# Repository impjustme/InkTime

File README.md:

# InkTime

InkTime este un smartwatch open-source cu consum redus, construit in jurul microcontroller-ului nRF52840, cu ecran e-paper, alimentare din baterie Li-Po, incarcare prin USB-C, monitorizare baterie, IMU si feedback haptic. Platforma a fost proiectata pentru autonomie buna, dimensiuni compacte si integrare mecanica intr-o carcasa dedicata.

## Diagrama bloc

```
                                +----------------------+
                                |       USB-C          |
                                |   alimentare / USB   |
                                +----------+-----------+
                                           |
                                           v
                                +----------------------+
                                |   ESD Protection     |
                                |    USBLC6-2SC6Y      |
                                +----------+-----------+
                                           |
                                           v
                                +----------------------+
                                |  Li-Po Charger       |
                                |    BQ25180YBGR       |
                                +----+------------+----+
                                     |            |
                                     |            +--------------------+
                                     |                                 |
                                     v                                 v
                           +-------------------+             +-------------------+
                           |    Li-Po Battery  |             |   Fuel Gauge      |
                           |     LP502030      |<-- I2C ---> |    MAX17048       |
                           +---------+---------+             +-------------------+
                                     |
                                     v
                           +-------------------+
                           |  Buck-Boost DC/DC |
                           |    RT6160AWSC     |
                           +---------+---------+
                                     |
                                   3V3/VREG
                                     |
        +----------------------------+------------------------------+
        |                            |                              |
        v                            v                              v
+---------------+          +-------------------+          +-------------------+
|   nRF52840    |<--I2C--->|      BMA423       |<--I2C--->|     DRV2605       |
| BLE MCU       |          |       IMU         |          |   Haptic Driver   |
+-------+-------+          +-------------------+          +---------+---------+
        |                                                              |
        | SPI + GPIO                                                    v
        v                                                      +----------------+
+-------------------+                                          | Vibration Motor |
| 1.54" E-Paper     |                                          |    10 x 2.7 mm  |
| via FPC connector |                                          +----------------+
+-------------------+
        |
        +--> boost / gate drive pentru EPD:
             MOSFET-uri + diode Schottky + inductoare + condensatori
```

## BoM

| Componenta       | Part number / Valoare  | Rol                           | Link JLC / sursa              | Datasheet                                                                                                                                                                              |
| ---------------- | ---------------------- | ----------------------------- | ----------------------------- | -------------------------------------------------------------------------------------------------------------------------------------------------------------------------------------- |
| MCU              | nRF52840               | microcontroller principal BLE | JLC Parts / external sourcing | [https://infocenter.nordicsemi.com/pdf/nRF52840_PS_v1.1.pdf](https://infocenter.nordicsemi.com/pdf/nRF52840_PS_v1.1.pdf)                                                               |
| PMIC charger     | BQ25180YBGR            | incarcare Li-Po prin USB-C    | JLC Parts                     | [https://www.ti.com/lit/ds/symlink/bq25180.pdf](https://www.ti.com/lit/ds/symlink/bq25180.pdf)                                                                                         |
| DC/DC            | RT6160AWSC             | conversie VBAT -> 3V3/VREG    | JLC Parts / external sourcing | [https://www.richtek.com/assets/product_file/RT6160A/DS6160A-05.pdf](https://www.richtek.com/assets/product_file/RT6160A/DS6160A-05.pdf)                                               |
| Fuel gauge       | MAX17048G+T10          | monitorizare baterie          | JLC Parts / external sourcing | [https://www.analog.com/media/en/technical-documentation/data-sheets/max17048-max17049.pdf](https://www.analog.com/media/en/technical-documentation/data-sheets/max17048-max17049.pdf) |
| IMU              | BMA423                 | accelerometru triaxial        | JLC Parts / external sourcing | [https://www.bosch-sensortec.com/products/motion-sensors/accelerometers/bma423/](https://www.bosch-sensortec.com/products/motion-sensors/accelerometers/bma423/)                       |
| Haptic driver    | DRV2605YZFR            | comanda motorului de vibratie | JLC Parts / external sourcing | [https://www.ti.com/lit/ds/symlink/drv2605.pdf](https://www.ti.com/lit/ds/symlink/drv2605.pdf)                                                                                         |
| ESD USB          | USBLC6-2SC6Y           | protectie ESD pentru USB      | JLC Parts                     | [https://www.st.com/resource/en/datasheet/usblc6-2.pdf](https://www.st.com/resource/en/datasheet/usblc6-2.pdf)                                                                         |
| Antena           | 2450AT18B100E          | antena 2.4 GHz                | external sourcing             | [https://www.johansontechnology.com/datasheets/antennas/2450AT18B100.pdf](https://www.johansontechnology.com/datasheets/antennas/2450AT18B100.pdf)                                     |
| Conector debug   | TC2030-IDC             | SWD / debugging               | external sourcing             | [https://www.tag-connect.com/product/tc2030-idc](https://www.tag-connect.com/product/tc2030-idc)                                                                                       |
| Conector display | 503480-2400            | conector FPC pentru e-paper   | external sourcing             | [https://www.molex.com/en-us/products/part-detail/5034802400](https://www.molex.com/en-us/products/part-detail/5034802400)                                                             |
| USB-C            | KH-TYPE-C-16P          | alimentare si interfata USB   | JLC Parts / external sourcing |                                                                                                                                                              |
| Cristal HF       | 32 MHz, SMD 2016       | ceas principal MCU            | JLC Parts / external sourcing |                                                                                                                                                                 |
| Cristal LF       | 32.768 kHz, SMD 3215   | RTC / low-power clock         | JLC Parts / external sourcing |                                                                                                                                                                 |
| MOSFET EPD       | SI1308EDL-T1-GE3       | comanda in etajul e-paper     | JLC Parts / external sourcing | [https://www.vishay.com/docs/68986/si1308edl.pdf](https://www.vishay.com/docs/68986/si1308edl.pdf)                                                                                     |
| MOSFET EPD       | DMG2305UX-7 / echiv.   | comanda in etajul e-paper     | JLC Parts / external sourcing | [https://www.diodes.com/assets/Datasheets/DMG2305UX.pdf](https://www.diodes.com/assets/Datasheets/DMG2305UX.pdf)                                                                       |
| Diode Schottky   | MBR0530                | etaj boost / redresare EPD    | JLC Parts / external sourcing | [https://www.onsemi.com/pdf/datasheet/mbr0530t1-d.pdf](https://www.onsemi.com/pdf/datasheet/mbr0530t1-d.pdf)                                                                           |
| Inductor power   | FTC252012SR47MBCA      | inductor pentru RT6160        | JLC Parts                     | [https://jlcpcb.com/partdetail/6763488-FTC252012SR47MBCA/C5832368](https://jlcpcb.com/partdetail/6763488-FTC252012SR47MBCA/C5832368)                                                   |
| Inductor EPD     | 68uH                   | inductor pentru boost EPD     | JLC Parts / external sourcing |                                                                                                                                                                  |
| Butoane          | EVP-AKE31A             | interfata utilizator          | JLC Parts / external sourcing |                                                                                                                                                                  |
| Baterie          | LP502030, 3.7V, 250mAh | sursa principala de energie   | external sourcing             |                                                                                                                                                       |
| Display          | 1.54" e-paper, 200x200 | afisaj principal              | external sourcing             |                                                                                                                                                                |
| Shaker           | 10 x 2.7 mm            | vibratie / feedback haptic    | external sourcing             |                                                                                                                                                               |
## Descriere hardware
1. Microcontroller principal

Sistemul este construit in jurul nRF52840, un microcontroller ARM Cortex-M4F cu BLE 5.x, suficient de performant pentru gestionarea afisajului e-paper, a senzorilor, a starii de baterie si a interfetei de utilizator.Pe partea de clock sunt folosite doua surse:

-un cristal de 32 MHz pentru clock-ul principal.

-un cristal de 32.768 kHz pentru RTC si scenarii low-power.

2. Alimentare si management energetic

Arhitectura de alimentare este impartita in trei blocuri.

BQ25180YBGR

Gestioneaza incarcarea bateriei Li-Po din USB-C. Intrarea de 5 V vine din VBUS, iar iesirea este conectata la bateria de o celula. Acest circuit este configurabil si monitorizabil, iar pinul de interrupt este dus catre MCU.

MAX17048

Monitorizeaza tensiunea si starea bateriei. Acesta comunica pe I2C cu microcontrollerul si expune un semnal de alerta pentru praguri critice sau schimbari de stare.

RT6160AWSC

Converteaza tensiunea bateriei intr-o alimentare stabila pentru sistemul digital. Acesta este blocul care alimenteaza rail-urile de lucru ale placii si perifericele sale.

In proiect, bateria nu este conectata printr-un conector JST clasic, ci direct la doua test pad-uri dedicate de pe PCB, una pentru VBAT si una pentru GND, pentru economie de spatiu.

3. Afisaj

Afisajul utilizat este un e-paper de 1.54", conectat printr-un conector FPC. Comunicatia cu MCU se face in principal prin SPI, iar pentru control sunt folosite si semnale GPIO dedicate:

CS

DC

RST

BUSY

Deoarece e-paper-ul necesita tensiuni si secvente specifice, exista un etaj discret dedicat pentru generarea si comutarea semnalelor de alimentare ale panelului, construit cu:

MOSFET-uri

diode Schottky

inductoare

condensatori de filtrare si bootstrap

4. IMU

BMA423 este accelerometrul triaxial folosit pentru detectie de miscare, pasi, gesturi si evenimente de trezire. Comunicatia se face pe I2C, iar semnalele de intrerupere sunt aduse pe GPIO-uri separate ale MCU-ului pentru reactii rapide si trezire din moduri low-power.

5. Feedback haptic

DRV2605 comanda un motor de vibratie compact. Comunicatia cu MCU se face pe I2C, iar activarea poate fi controlata si printr-un semnal GPIO dedicat. Acest bloc ofera feedback tactil pentru navigare, notificari si interactiuni de baza.

6. USB-C si protectie

Interfata USB-C este folosita pentru alimentare si, optional, interfata USB a microcontrollerului. Liniile sensibile sunt protejate cu USBLC6-2SC6Y. Liniile CC sunt terminate corespunzator pentru a permite functionarea corecta ca device.

7. RF si antena

Conectivitatea radio este realizata prin antena chip 2.4 GHz si o retea de matching RF. Antena este pozitionata la marginea PCB-ului, iar sub ea exista zona de keepout fara trasee si fara plan de masa, pentru a nu degrada performanta RF.

## Pini folositi

| Pin nRF52840  | Semnal         | Destinatie                                     | Motiv                             |
| ------------- | -------------- | ---------------------------------------------- | --------------------------------- |
| P0.00 / XL1   | XL1            | cristal 32.768 kHz                             | clock low-power / RTC             |
| P0.01 / XL2   | XL2            | cristal 32.768 kHz                             | clock low-power / RTC             |
| P0.04         | IMU_INT1       | BMA423                                         | intrerupere senzor                |
| P0.05         | IMU_INT2       | BMA423                                         | intrerupere senzor                |
| P0.06         | EPD_CS         | e-paper                                        | selectie SPI display              |
| P0.07         | EPD_DC         | e-paper                                        | selectie data/comanda             |
| P0.08         | EPD_RST        | e-paper                                        | reset display                     |
| P0.09         | PMIC_INT       | BQ25180                                        | interrupt charger / PMIC          |
| P0.11         | SPI_SCK        | e-paper                                        | clock SPI                         |
| P0.12         | SPI_MOSI       | e-paper                                        | date SPI                          |
| P0.13         | EPD_BUSY       | e-paper                                        | busy status display               |
| P0.14         | I2C_SCL        | BMA423 / DRV2605 / MAX17048 / BQ25180 / RT6160 | magistrala I2C comuna             |
| P0.15         | I2C_SDA        | BMA423 / DRV2605 / MAX17048 / BQ25180 / RT6160 | magistrala I2C comuna             |
| P0.18 / RESET | RESET          | sistem                                         | reset hardware                    |
| P0.19         | HAPTIC_EN      | DRV2605                                        | enable local pentru blocul haptic |
| P0.26         | SW_UP          | buton                                          | input utilizator                  |
| P0.27         | SW_DN          | buton                                          | input utilizator                  |
| P1.00         | SW_ENT         | buton                                          | input utilizator                  |
| P1.01         | ALERT          | MAX17048                                       | alerta fuel gauge                 |
| P1.09         | SWO            | debug                                          | trace / debugging                 |
| XC1 / XC2     | 32 MHz crystal | clock principal                                | stabilitate si RF                 |
| ANT           | RF             | antena + matching                              | transmisie radio BLE              |
| SWDIO         | debug          | TC2030-IDC                                     | programare / debug                |
| SWDCLK        | debug          | TC2030-IDC                                     | programare / debug                |
| VBUS          | alimentare USB | USB-C                                          | intrare 5 V                       |
| D+ / D-       | USB data       | USB-C prin protectie ESD                       | interfata USB                     |

## PCB

Layer stack

Structura folosita:

Top - componente, rutare semnale, poligoane GND locale

Route2 - plan principal de masa / referinta

Route15 - rutare interna suplimentara pentru semnale si distributie

Bottom - rutare suplimentara si zone GND

## Design log

In procesul de layout au fost acceptate:

1. SMD - via / pin overlap

In zone foarte dense, in special langa capsule mici si in fanout-ul unor componente fine-pitch, anumite vias au fost plasate direct pe pini ai componentelor.

3. Copper width warnings

Pe rail-urile de putere s-a urmarit 0.3 mm acolo unde spatiul permite. In fanout-uri foarte scurte, imediat la iesirea din pini foarte mici sau intre componente apropiate, au ramas segmente locale mai inguste. Distributia principala de putere a fost mentinuta lata, iar exceptiile sunt limitate la zonele de iesire.

4. Board outline / edge related warnings

Elementele de interfata ale produsului, in special anumite butoane si zona conectorului, au fost aliniate mecanic cu produsul final. Acolo unde apar avertizari de proximitate fata de conturul placii, acestea au fost evaluate din punct de vedere mecanic si acceptate daca nu afecteaza functionalitatea.

5. Unghiuri drepte locale
   
Desi rutarea a fost facuta preponderent fara colturi de 90 de grade, au ramas cateva unghiuri drepte locale in zone foarte aglomerate. Acestea au fost mentinute doar acolo unde alternativele cresteau numarul de vias sau complicau excesiv rutarea.

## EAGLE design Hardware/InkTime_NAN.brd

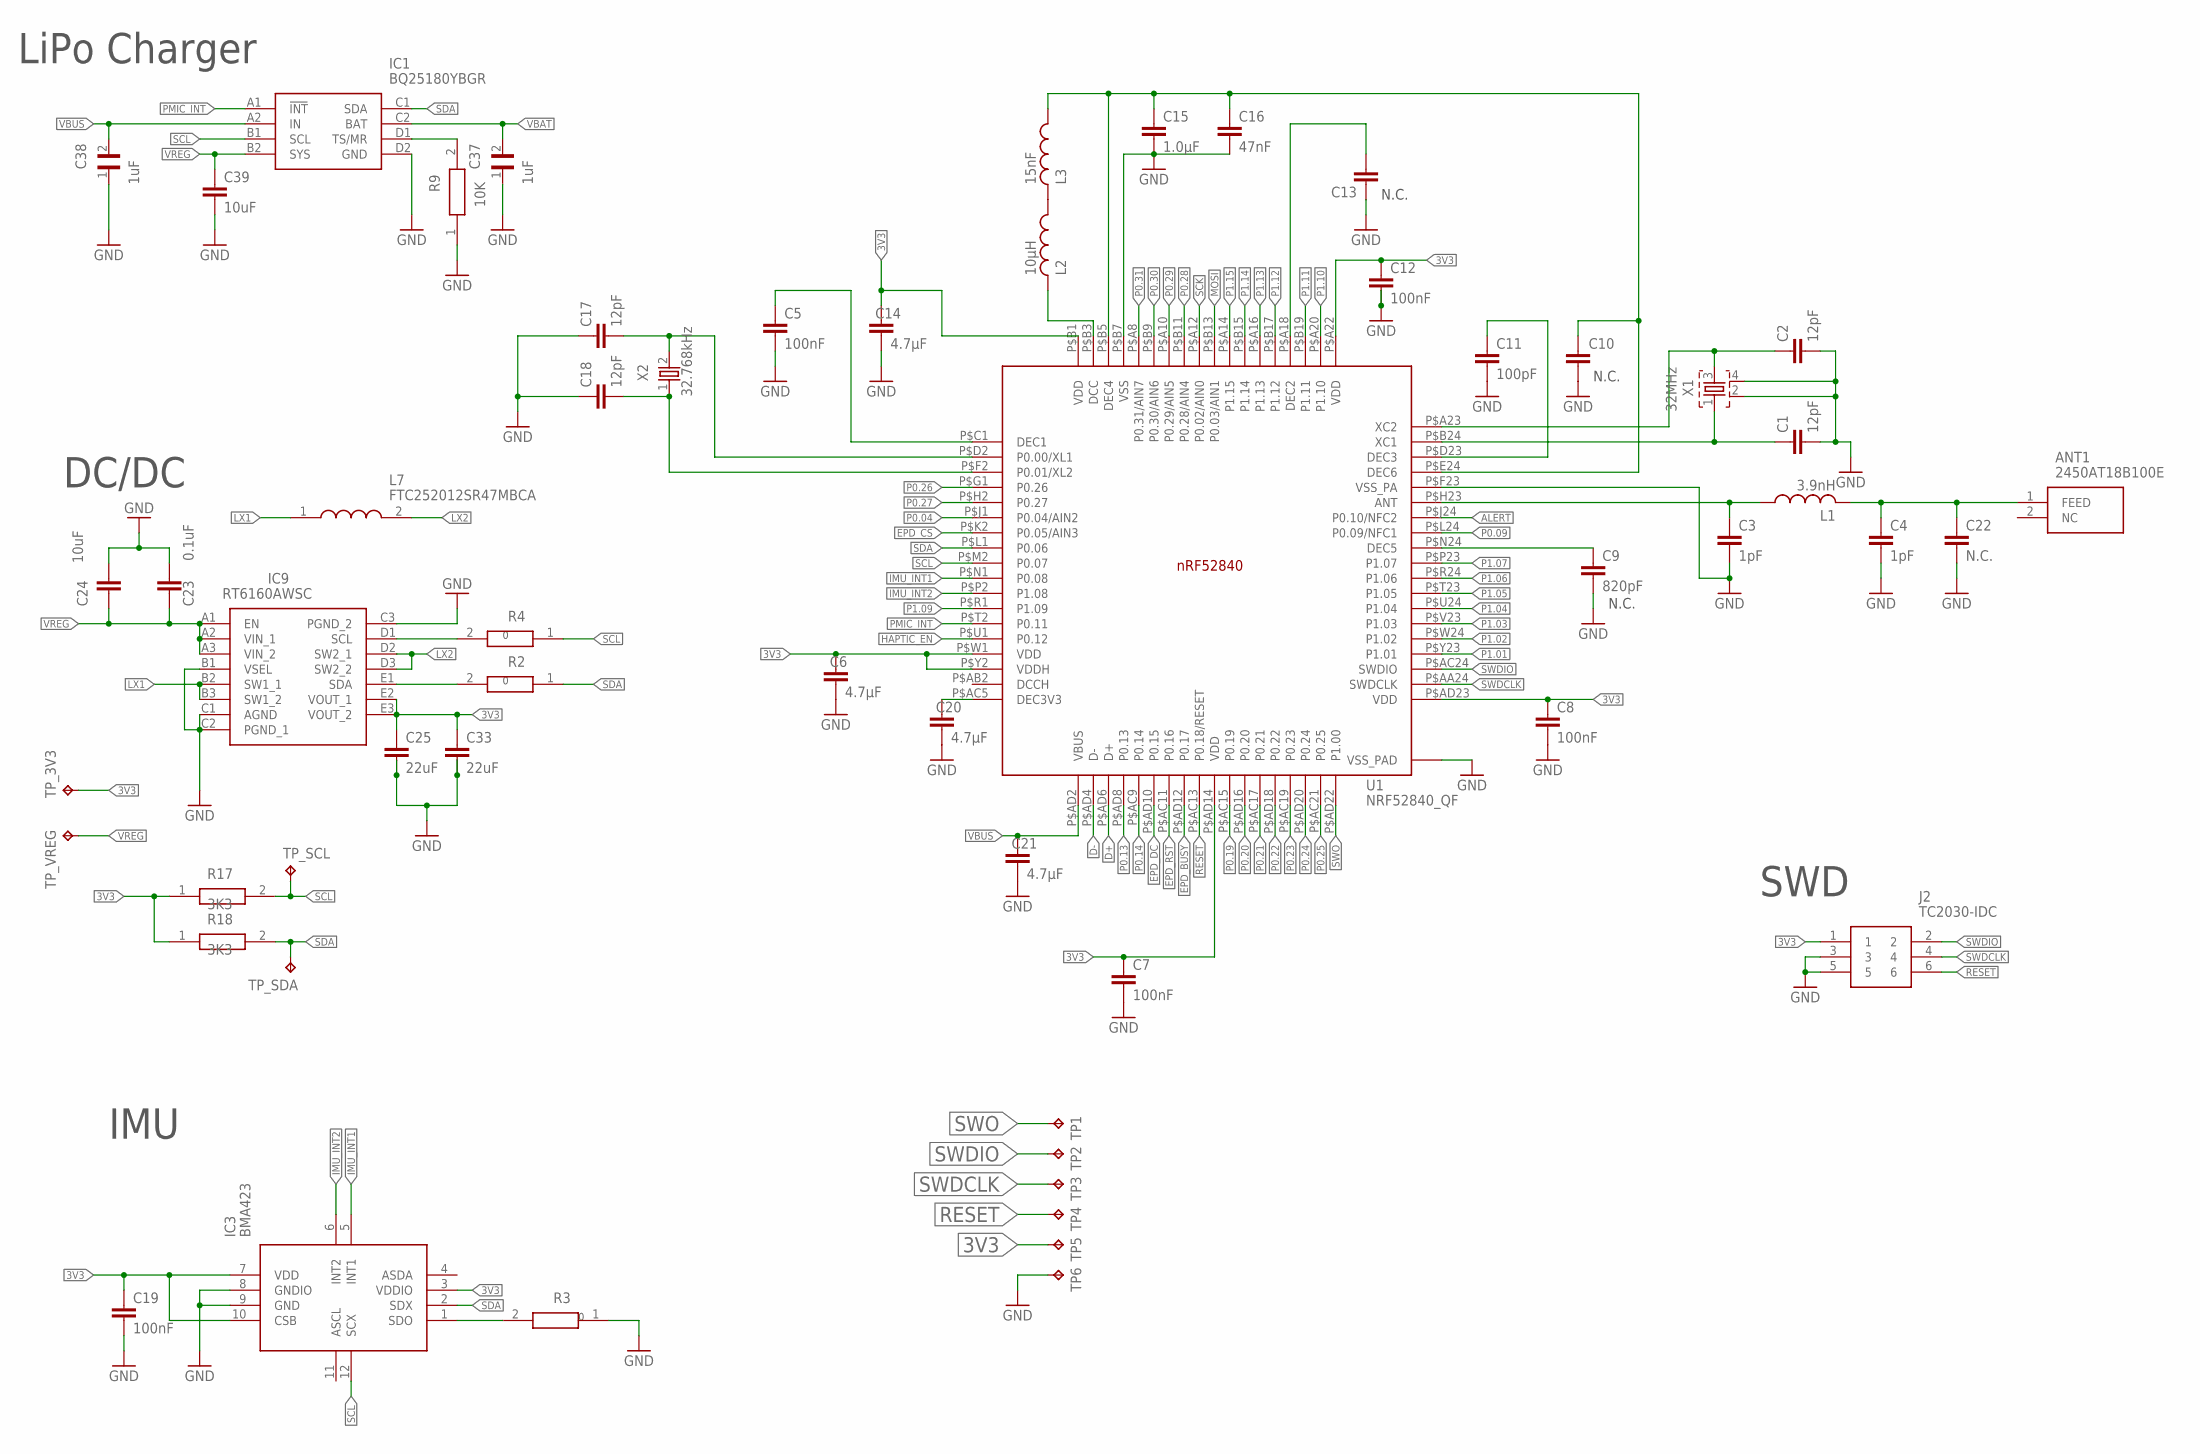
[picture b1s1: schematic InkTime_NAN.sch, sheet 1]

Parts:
ANT1: 2450AT18B100E; 2450AT18B100E_ANTC3216X140N
C1, C2, C17, C18: 12pF; NORDIC_NRF_3_RESC0201_L
C3, C4: 1pF; NORDIC_NRF_3_RESC0201_L
C5, C7, C8, C12, C19: 100nF; NORDIC_NRF_3_RESC0201_L
C6, C14, C20, C21: 4.7µF; NORDIC_NRF_3_RESC0402_L
C9: 820pF; NORDIC_NRF_3_RESC0201_L
C10, C13: NORDIC_NRF_3_CAPACITOR_0201_L; NORDIC_NRF_3_RESC0201_L
C11: 100pF; NORDIC_NRF_3_RESC0201_L
C15: 1.0µF; NORDIC_NRF_3_RESC0402_L
C16: 47nF; NORDIC_NRF_3_RESC0201_L
C22: N.C.; NORDIC_NRF_3_RESC0201_L
C23: 0.1uF; NORDIC_NRF_3_RESC0201_L
C24, C39: 10uF; NORDIC_NRF_3_RESC0402_L
C25, C33: 22uF; NORDIC_NRF_3_RESC0402_L
C37, C38: 1uF; GRM011R60J152KE01L_2_CAPC0201X13N
IC1: BQ25180YBGR; BQ25180YBGR_BGA8C40P2X4_100X155X50
IC3: BMA423; BMA423_BMA423
IC9: RT6160AWSC; RT6160AWSC_BGA15C40P3X5_140X230X60
J2: TC2030-IDC; TC2030-IDC_TC2030IDC
L1: 3.9nH; NORDIC_NRF_2_RESC0402_L
L2: 10µH; NORDIC_NRF_2_RESC0402_L
L3: 15nF; NORDIC_NRF_2_RESC0402_L
L7: FTC252012SR47MBCA; MLP2016SR47MT0S1_INDC2016X100N
R2, R3, R4: CPF0201D7K68C1_CPF0201D7K68C1; CPF0201D7K68C1_0201
R9: 10K; CPF0201D7K68C1_0201
R17, R18: 3K3; CPF0201D7K68C1_0201
TP1, TP2, TP3, TP4, TP5, TP6: HECTOR_WATCH_1_TPTP20R; HECTOR_WATCH_1_TP20R
TP_3V3: HECTOR_WATCH_1_TPTP20R; HECTOR_WATCH_1_TP20R
TP_SCL: HECTOR_WATCH_1_TPTP20R; HECTOR_WATCH_1_TP20R
TP_SDA: HECTOR_WATCH_1_TPTP20R; HECTOR_WATCH_1_TP20R
TP_VREG: HECTOR_WATCH_1_TPTP20R; HECTOR_WATCH_1_TP20R
U1: NRF52840_QF; NORDIC_NRF_4_AQFN50P700X700X85_HS-74N
X1: 32MHz; NORDIC_NRF_BT-XTAL_2016_N
X2: 32.768kHz; NORDIC_NRF_1_XTAL_3215_N

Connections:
3V3: C6.1, C7.1, C8.1, C12.1, C14.1, C19.1, C25.1, C33.1, IC3.3 (VDDIO), IC3.7 (VDD), IC3.10 (CSB), IC9.E2 (VOUT_1), IC9.E3 (VOUT_2), J2.1, R17.1, R18.1, TP5.TP, TP_3V3.TP, U1.P$A22 (VDD), U1.P$AD14 (VDD), U1.P$AD23 (VDD), U1.P$B1 (VDD), U1.P$W1 (VDD), U1.P$Y2 (VDDH); also elsewhere on the board
ALERT: U1.P$J24 (P0.10/NFC2); also elsewhere on the board
D+: U1.P$AD6 (D+); also elsewhere on the board
D-: U1.P$AD4 (D-); also elsewhere on the board
EPD_BUSY: U1.P$AD12 (P0.17); also elsewhere on the board
EPD_CS: U1.P$K2 (P0.05/AIN3); also elsewhere on the board
EPD_DC: U1.P$AD10 (P0.15); also elsewhere on the board
EPD_RST: U1.P$AC11 (P0.16); also elsewhere on the board
GND: C1.2, C2.2, C3.2, C4.2, C5.2, C6.2, C7.2, C8.2, C9.2, C10.1, C11.2, C12.2, C13.1, C14.2, C15.2, C16.2, C17.1, C18.1, C19.2, C20.2, C21.2, C22.2, C23.1, C24.1, C25.2, C33.2, C37.1, C38.1, C39.2, IC1.D2 (GND), IC3.8 (GNDIO), IC3.9 (GND), IC9.B1 (VSEL), IC9.C1 (AGND), IC9.C2 (PGND_1), IC9.C3 (PGND_2), J2.3, J2.5, R3.1, R9.1, TP6.TP, U1.P$74 (VSS_PAD), U1.P$75 (VSS_PAD), U1.P$76 (VSS_PAD), U1.P$77 (VSS_PAD), U1.P$78 (VSS_PAD), U1.P$79 (VSS_PAD), U1.P$80 (VSS_PAD), U1.P$81 (VSS_PAD), U1.P$82 (VSS_PAD), U1.P$83 (VSS_PAD), U1.P$84 (VSS_PAD), U1.P$85 (VSS_PAD), U1.P$86 (VSS_PAD), U1.P$87 (VSS_PAD), U1.P$88 (VSS_PAD), U1.P$89 (VSS_PAD), U1.P$90 (VSS_PAD), U1.P$B7 (VSS), U1.P$F23 (VSS_PA), X1.2, X1.4; also elsewhere on the board
HAPTIC_EN: U1.P$U1 (P0.12); also elsewhere on the board
IMU_INT1: IC3.5 (INT1), U1.P$N1 (P0.08)
IMU_INT2: IC3.6 (INT2), U1.P$P2 (P1.08)
LX1: IC9.B2 (SW1_1), IC9.B3 (SW1_2), L7.1
LX2: IC9.D2 (SW2_1), IC9.D3 (SW2_2), L7.2
MOSI: U1.P$B13 (P0.03/AIN1); also elsewhere on the board
unnamed: C5.1, U1.P$C1 (DEC1)
unnamed: C9.1, U1.P$N24 (DEC5)
unnamed: C11.1, U1.P$D23 (DEC3)
unnamed: IC9.D1 (SCL), R4.2
unnamed: C17.2, U1.P$D2 (P0.00/XL1), X2.2
unnamed: C18.2, U1.P$F2 (P0.01/XL2), X2.1
unnamed: C3.1, L1.1, U1.P$H23 (ANT)
unnamed: ANT1.1 (FEED), C4.1, C22.1, L1.2
unnamed: C10.2, C15.1, C16.1, L3.1, U1.P$B5 (DEC4), U1.P$E24 (DEC6)
unnamed: C2.1, U1.P$A23 (XC2), X1.3
unnamed: C1.1, U1.P$B24 (XC1), X1.1
unnamed: L2.1, L3.2
unnamed: L2.2, U1.P$B3 (DCC)
unnamed: C13.2, U1.P$A18 (DEC2)
unnamed: IC3.1 (SDO), R3.2
unnamed: C20.1, U1.P$AC5 (DEC3V3)
unnamed: IC9.E1 (SDA), R2.2
unnamed: IC1.D1 (TS/MR), R9.2
P0.04: U1.P$J1 (P0.04/AIN2)
P0.09: U1.P$L24 (P0.09/NFC1)
P0.13: U1.P$AD8 (P0.13); also elsewhere on the board
P0.14: U1.P$AC9 (P0.14); also elsewhere on the board
P0.19: U1.P$AC15 (P0.19)
P0.20: U1.P$AD16 (P0.20)
P0.21: U1.P$AC17 (P0.21)
P0.22: U1.P$AD18 (P0.22)
P0.23: U1.P$AC19 (P0.23)
P0.24: U1.P$AD20 (P0.24)
P0.25: U1.P$AC21 (P0.25)
P0.26: U1.P$G1 (P0.26)
P0.27: U1.P$H2 (P0.27)
P0.28: U1.P$B11 (P0.28/AIN4)
P0.29: U1.P$A10 (P0.29/AIN5)
P0.30: U1.P$B9 (P0.30/AIN6)
P0.31: U1.P$A8 (P0.31/AIN7)
P1.01: U1.P$Y23 (P1.01); also elsewhere on the board
P1.02: U1.P$W24 (P1.02); also elsewhere on the board
P1.03: U1.P$V23 (P1.03)
P1.04: U1.P$U24 (P1.04)
P1.05: U1.P$T23 (P1.05)
P1.06: U1.P$R24 (P1.06)
P1.07: U1.P$P23 (P1.07)
P1.09: U1.P$R1 (P1.09)
P1.10: U1.P$A20 (P1.10)
P1.11: U1.P$B19 (P1.11)
P1.12: U1.P$B17 (P1.12)
P1.13: U1.P$A16 (P1.13)
P1.14: U1.P$B15 (P1.14)
P1.15: U1.P$A14 (P1.15)
PMIC_INT: IC1.A1 (!INT), U1.P$T2 (P0.11)
RESET: J2.6, TP4.TP, U1.P$AC13 (P0.18/RESET)
SCK: U1.P$A12 (P0.02/AIN0); also elsewhere on the board
SCL: IC1.B1 (SCL), IC3.12 (SCX), R4.1, R17.2, TP_SCL.TP, U1.P$M2 (P0.07); also elsewhere on the board
SDA: IC1.C1 (SDA), IC3.2 (SDX), R2.1, R18.2, TP_SDA.TP, U1.P$L1 (P0.06); also elsewhere on the board
SWDCLK: J2.4, TP3.TP, U1.P$AA24 (SWDCLK)
SWDIO: J2.2, TP2.TP, U1.P$AC24 (SWDIO)
SWO: TP1.TP, U1.P$AD22 (P1.00)
VBAT: C37.2, IC1.C2 (BAT); also elsewhere on the board
VBUS: C21.1, C38.2, IC1.A2 (IN), U1.P$AD2 (VBUS); also elsewhere on the board
VREG: C23.2, C24.2, C39.1, IC1.B2 (SYS), IC9.A1 (EN), IC9.A2 (VIN_1), IC9.A3 (VIN_2), TP_VREG.TP

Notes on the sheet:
N.C.
SWD
IMU
DC/DC
LiPo Charger

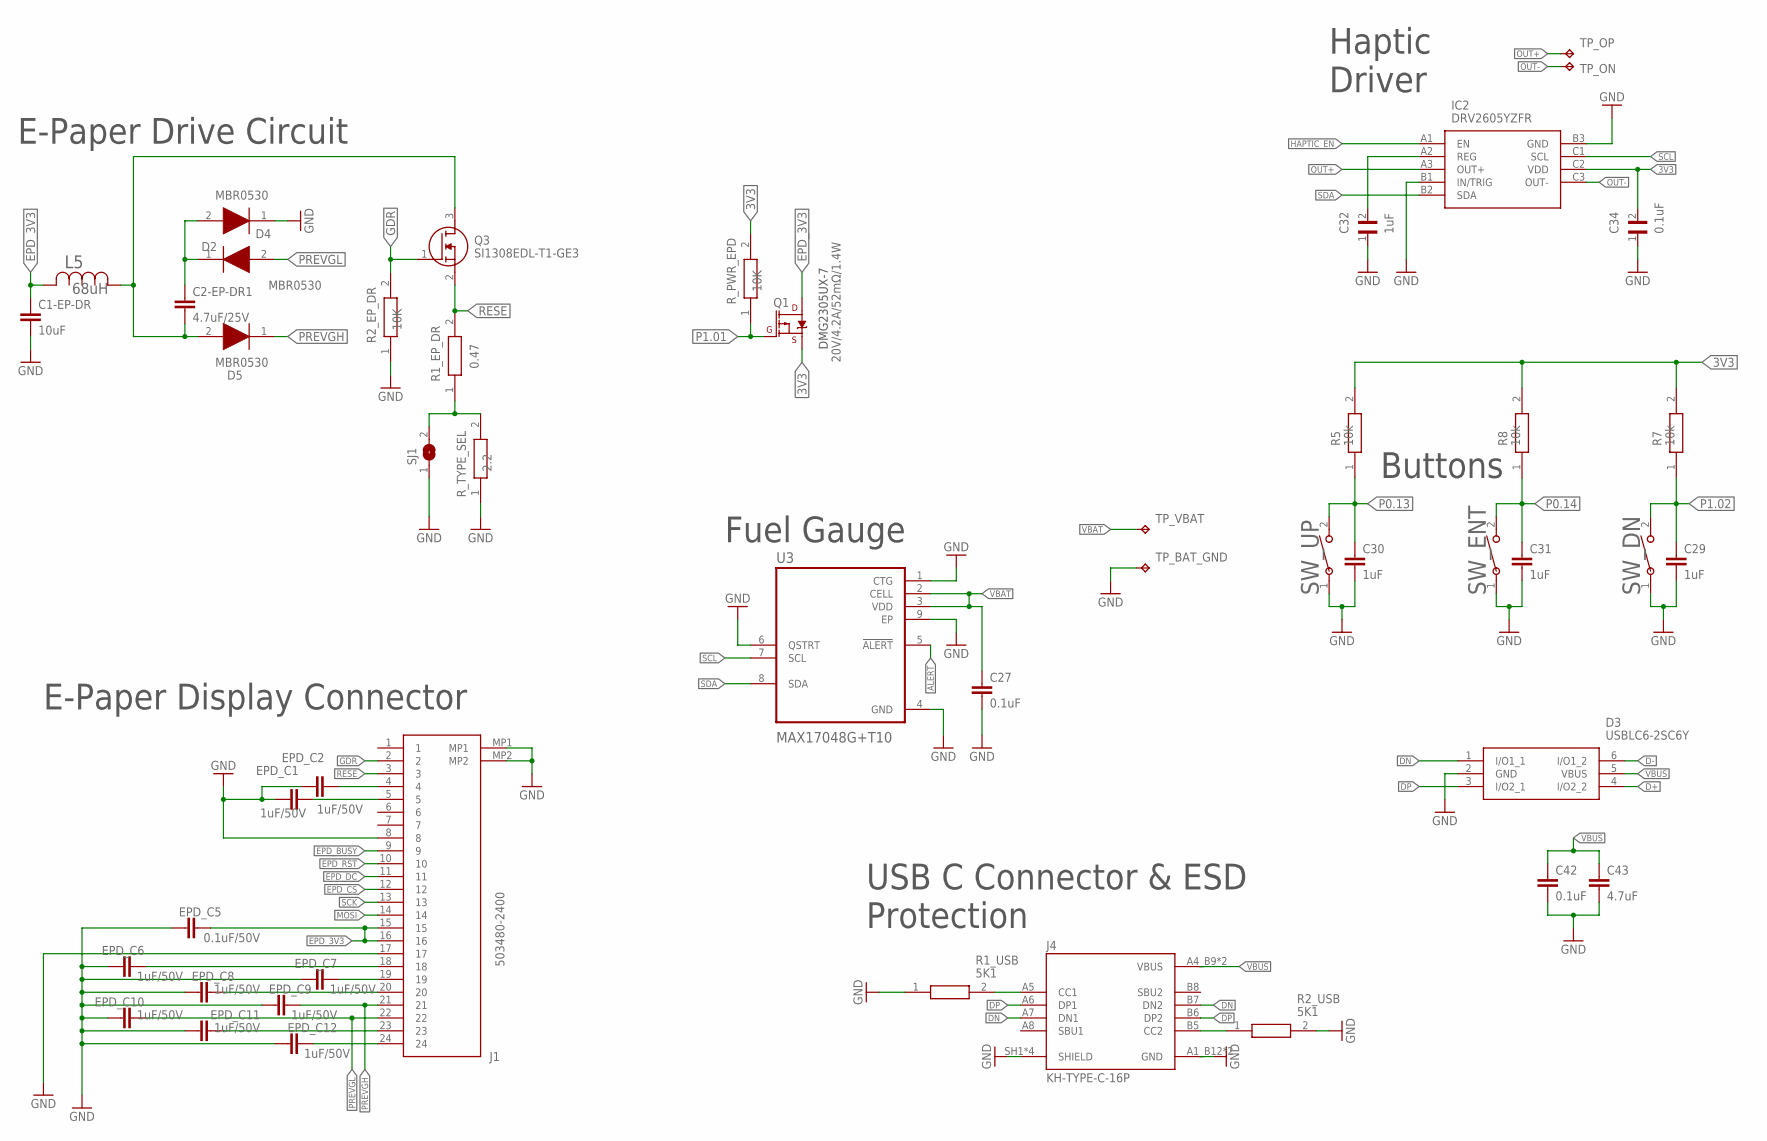
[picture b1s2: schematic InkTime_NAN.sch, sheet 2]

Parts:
C1-EP-DR: 10uF; NORDIC_NRF_3_RESC0402_L
C2-EP-DR1: 4.7uF/25V; NORDIC_NRF_3_RESC0402_L
C27, C42: 0.1uF; NORDIC_NRF_3_RESC0201_L
C29, C30, C31: 1uF; NORDIC_NRF_3_RESC0402_L
C32: 1uF; GRM011R60J152KE01L_2_CAPC0201X13N
C34: 0.1uF; GRM011R60J152KE01L_2_CAPC0201X13N
C43: 4.7uF; NORDIC_NRF_3_RESC0402_L
D2, D4, D5: MBR0530; ESP32_C6_LIBRARY_5_SOD3716X135N
D3: USBLC6-2SC6Y; ESP32_C6_LIBRARY_3_SOT95P280X145-6N
EPD_C1, EPD_C2, EPD_C6, EPD_C7, EPD_C8, EPD_C9, EPD_C10, EPD_C11, EPD_C12: 1uF/50V; NORDIC_NRF_3_RESC0402_L
EPD_C5: 0.1uF/50V; NORDIC_NRF_3_RESC0201_L
IC2: DRV2605YZFR; DRV2605YZFR_BGA9C50P3X3_144X144X62
J1: 503480-2400; 503480-2400_5034802400
J4: KH-TYPE-C-16P; KH-TYPE-C-16P_KINGHELM_KH-TYPE-C-16P
L5: 68uH; ESP32_C6_LIBRARY_2_IND_4828-WE-TPC_WRE
Q1: 20V/4.2A/52mΩ/1.4W; ESP32_C6_LIBRARY_4_ESP32_C6_LIBRARY_4_ESP32_C6_LIBRARY_4_ES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
Q3: SI1308EDL-T1-GE3; ESP32_C6_LIBRARY_6_SOT65P210X110-3N
R1_EP_DR: 0.47; CPF0201D7K68C1_0201
R1_USB, R2_USB: 5K1; ERA-1AEB3401C_0201
R2_EP_DR: 10K; CPF0201D7K68C1_0201
R5, R7, R8: 10k; CPF0201D7K68C1_0201
R_PWR_EPD: 10K; CPF0201D7K68C1_0201
R_TYPE_SEL: 2.2; CPF0201D7K68C1_0201
SJ1: ESP32_C6_LIBRARY_7_JUMPER_SJ
SW_DN: 2025-10-22_07-23-44_LIBRARY_EVP-AKE31ASW_EVP-AKE3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; 2025-10-22_07-23-44_LIBRARY_SW_EVP-AKE31A_PAN
SW_ENT: SW_ENT; 2025-10-22_07-23-44_LIBRARY_SW_EVP-AKE31A_PAN
SW_UP: 2025-10-22_07-23-44_LIBRARY_EVP-AKE31ASW_EVP-AKE3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; 2025-10-22_07-23-44_LIBRARY_SW_EVP-AKE31A_PAN
TP_BAT_GND: HECTOR_WATCH_1_TPTP20R; HECTOR_WATCH_1_TP20R
TP_ON: HECTOR_WATCH_1_TPTP20R; HECTOR_WATCH_1_TP20R
TP_OP: HECTOR_WATCH_1_TPTP20R; HECTOR_WATCH_1_TP20R
TP_VBAT: HECTOR_WATCH_1_TPTP20R; HECTOR_WATCH_1_TP20R
U3: MAX17048G+T10; ESP32_C6_LIBRARY_SON50P200X200X80-9N

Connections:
3V3: C34.2, IC2.C2 (VDD), Q1.2 (S), R5.2, R7.2, R8.2, R_PWR_EPD.2; also elsewhere on the board
ALERT: U3.5 (!ALERT); also elsewhere on the board
D+: D3.4 (I/O2_2); also elsewhere on the board
D-: D3.6 (I/O1_2); also elsewhere on the board
DN: D3.1 (I/O1_1), J4.A7 (DN1), J4.B7 (DN2)
DP: D3.3 (I/O2_1), J4.A6 (DP1), J4.B6 (DP2)
EPD_3V3: C1-EP-DR.1, EPD_C5.2, J1.15, J1.16, L5.2, Q1.3 (D)
EPD_BUSY: J1.9; also elsewhere on the board
EPD_CS: J1.12; also elsewhere on the board
EPD_DC: J1.11; also elsewhere on the board
EPD_RST: J1.10; also elsewhere on the board
GDR: J1.2, Q3.1 (G), R2_EP_DR.2
GND: C1-EP-DR.2, C27.2, C29.2, C30.2, C31.2, C32.1, C34.1, C42.2, C43.2, D2.1 (K), D3.2 (GND), EPD_C1.1, EPD_C2.1, EPD_C5.1, EPD_C6.1, EPD_C7.1, EPD_C8.1, EPD_C9.1, EPD_C10.1, EPD_C11.1, EPD_C12.1, IC2.B1 (IN/TRIG), IC2.B3 (GND), J1.8, J1.17, J1.MP1, J1.MP2, J4.A1_B12 (GND), J4.A12_B1 (GND), J4.SH1 (SHIELD), J4.SH2 (SHIELD), J4.SH3 (SHIELD), J4.SH4 (SHIELD), R1_USB.1, R2_EP_DR.1, R2_USB.2, R_TYPE_SEL.1, SJ1.1, SW_DN.1, SW_ENT.1, SW_UP.1, TP_BAT_GND.TP, U3.1 (CTG), U3.4 (GND), U3.6 (QSTRT), U3.9 (EP); also elsewhere on the board
HAPTIC_EN: IC2.A1 (EN); also elsewhere on the board
MOSI: J1.14; also elsewhere on the board
unnamed: C2-EP-DR1.2, D5.2 (A), L5.1, Q3.3 (D)
unnamed: EPD_C8.2, J1.20
unnamed: C2-EP-DR1.1, D2.2 (A), D4.1 (K)
unnamed: EPD_C2.2, J1.4
unnamed: R1_EP_DR.1, R_TYPE_SEL.2, SJ1.2
unnamed: EPD_C1.2, J1.5
unnamed: C32.2, IC2.A2 (REG)
unnamed: J4.B5 (CC2), R2_USB.1
unnamed: J4.A5 (CC1), R1_USB.2
unnamed: EPD_C7.2, J1.19
unnamed: EPD_C6.2, J1.18
unnamed: EPD_C11.2, J1.23
unnamed: EPD_C12.2, J1.24
OUT+: IC2.A3 (OUT+), TP_OP.TP
OUT-: IC2.C3 (OUT-), TP_ON.TP
P0.13: C30.1, R5.1, SW_UP.2; also elsewhere on the board
P0.14: C31.1, R8.1, SW_ENT.2; also elsewhere on the board
P1.01: Q1.1 (G), R_PWR_EPD.1; also elsewhere on the board
P1.02: C29.1, R7.1, SW_DN.2; also elsewhere on the board
PREVGH: D5.1 (K), EPD_C9.2, J1.21
PREVGL: D4.2 (A), EPD_C10.2, J1.22
RESE: J1.3, Q3.2 (S), R1_EP_DR.2
SCK: J1.13; also elsewhere on the board
SCL: IC2.C1 (SCL), U3.7 (SCL); also elsewhere on the board
SDA: IC2.B2 (SDA), U3.8 (SDA); also elsewhere on the board
VBAT: C27.1, TP_VBAT.TP, U3.2 (CELL), U3.3 (VDD); also elsewhere on the board
VBUS: C42.1, C43.1, D3.5 (VBUS), J4.A4_B9 (VBUS), J4.A9_B4 (VBUS); also elsewhere on the board

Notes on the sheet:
DMG2305UX-7
E-Paper Drive Circuit
Haptic Driver
Buttons
Fuel Gauge
E-Paper Display Connector
USB C Connector & ESD Protection

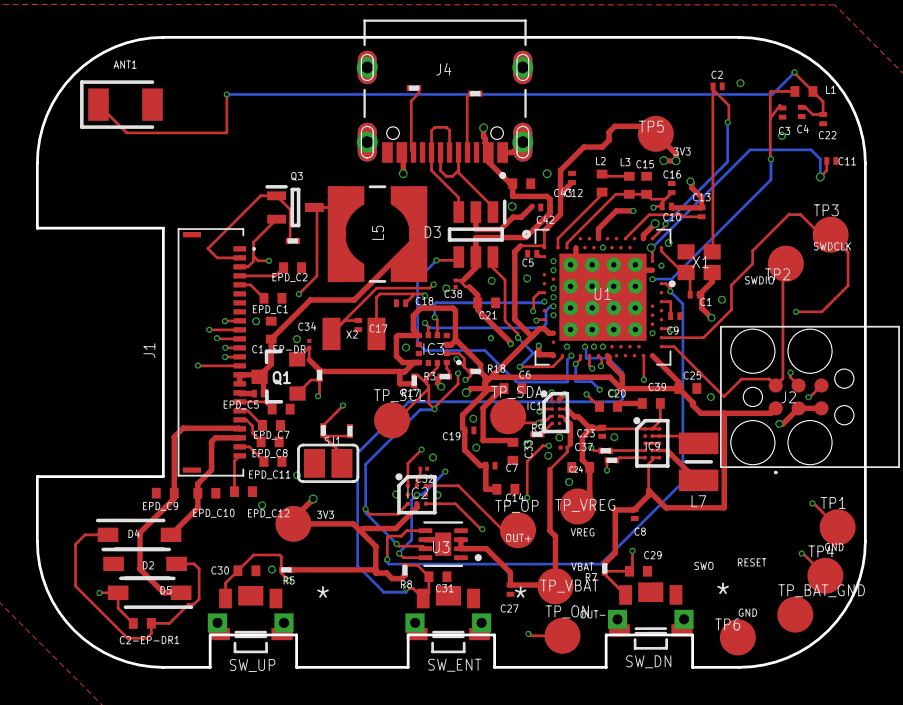
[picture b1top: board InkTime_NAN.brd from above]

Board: 4 copper layers, 46.0 x 35.0 mm, 105 parts (0 on the bottom side), 70 nets.

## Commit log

2026-04-10 Add Apache License 2.0
    Added Apache License 2.0 to the project.
2026-04-19 Create Images Folder
2026-04-19 Delete
2026-04-19 Create aux
2026-04-20 Enhance README
2026-04-20 Added step file as zip, due to file size

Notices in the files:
parts and their libraries:
COPYRIGHT: Copyright (C) 2024 Ultra Librarian. All rights reserved.
COPYRIGHT: Copyright (C) 2025 Ultra Librarian. All rights reserved.
